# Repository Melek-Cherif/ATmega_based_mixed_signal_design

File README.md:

# ATmega328P Mixed-Signal Design  
*A KiCad PCB project for [Mastering KiCAD: Open source PCB design for beginners] on Coursera.*  

---
## 📷 Preview  
### PCB Layout  

### 3D View  

---

## 📌 Key Features  
- ATmega328P with ADC signal conditioning.  
- Proper decoupling (100nF on ARef, AVCC).  
- Optimized mixed-signal layout.  

---

## 🛠️ Repository Structure  

├── 📂 Mixed_Signal_Design/  
│   ├── 📄 Mixed_Signal_Design.kicad_pro    
│   ├── 📄 Mixed_Signal_Design.kicad_pcb    
│   ├── 📄 Mixed_Signal_Design.kicad_sch    
│   ├── 📂 schematics/
│   │   └── 📄 Mixed_Signal_Design.pdf      
│   └── 📂 fabrication_output/      
│       ├── 📂 BOM/
│       │   └── 📄 Mixed_Signal_Design.csv 
│       └── 📂 gerber/              
│                 
├── 📂 images/                      
│   ├── 📄 3d_view.png              
│   └── 📄 pcb_layout.png       
└── 📄 README.md

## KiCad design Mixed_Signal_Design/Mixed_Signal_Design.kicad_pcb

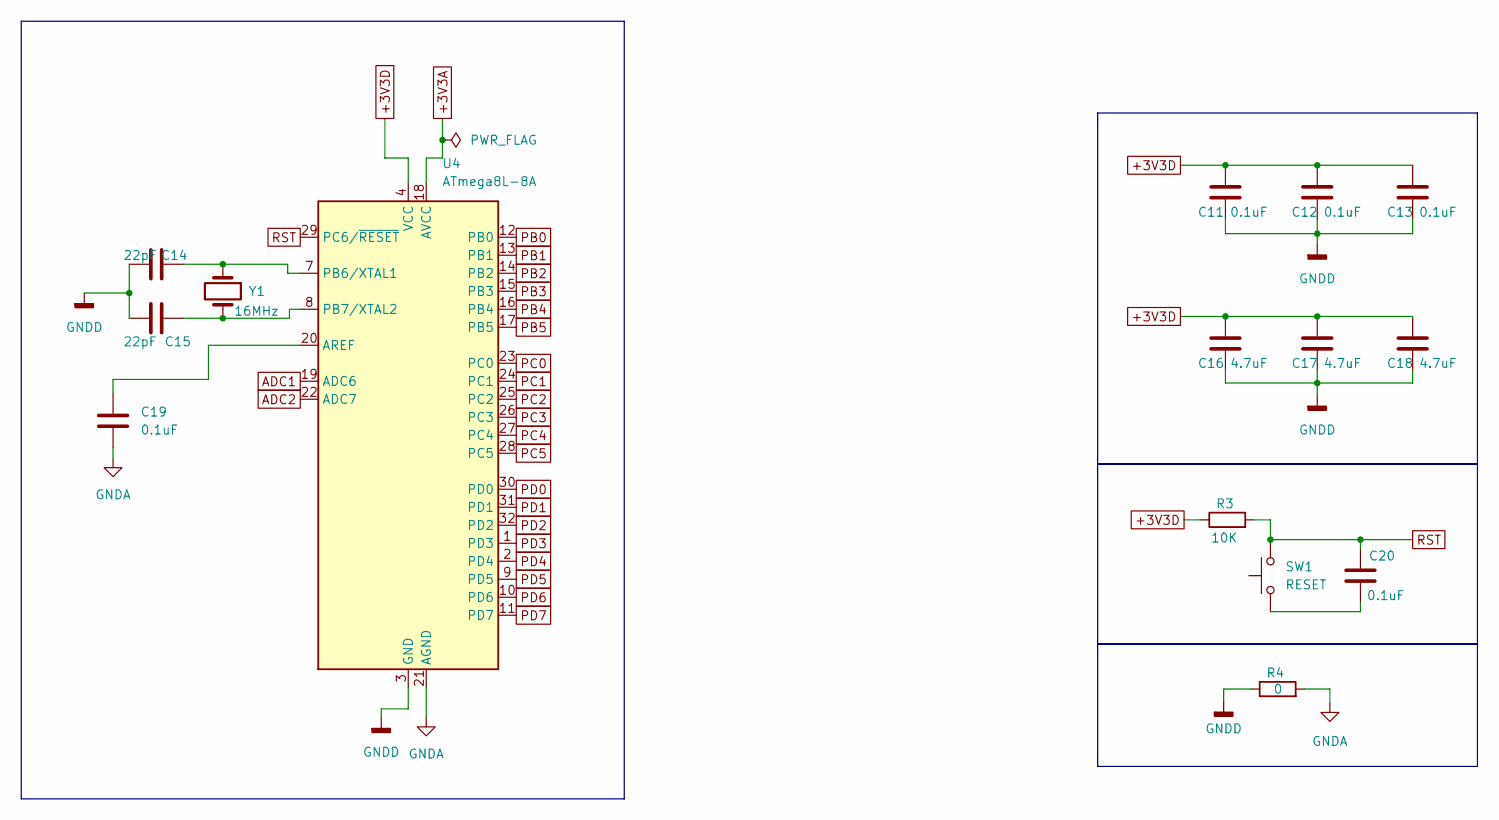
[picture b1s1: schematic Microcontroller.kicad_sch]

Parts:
C11, C12, C13, C19, C20: 0.1uF; C_0603_1608Metric
C14, C15: 22pF; C_0402_1005Metric
C16, C17, C18: 4.7uF; C_0603_1608Metric
R3: 10K; R_0402_1005Metric_Pad0.72x0.64mm_HandSolder
R4: 0; R_0402_1005Metric_Pad0.72x0.64mm_HandSolder
SW1: RESET; SW_SPST_B3U-1000P
U4: ATmega8L-8A; TQFP-32_7x7mm_P0.8mm
Y1: 16MHz; Crystal_SMD_HC49-SD

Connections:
+3V3A: U4.18 (AVCC); also elsewhere on the board
+3V3D: C11.1, C12.1, C13.1, C16.1, C17.1, C18.1, R3.1, U4.4 (VCC), U4.6 (VCC); also elsewhere on the board
ADC1: U4.19 (ADC6); also elsewhere on the board
ADC2: U4.22 (ADC7); also elsewhere on the board
GNDA: C19.1, R4.2, U4.21 (AGND); also elsewhere on the board
GNDD: C11.2, C12.2, C13.2, C14.1, C15.2, C16.2, C17.2, C18.2, R4.1, U4.3 (GND), U4.5 (GND); also elsewhere on the board
unnamed: C20.2, SW1.1 (A), SW1.2 (A)
unnamed: C19.2, U4.20 (AREF)
unnamed: C14.2, U4.7 (PB6/XTAL1), Y1.1
unnamed: C15.1, U4.8 (PB7/XTAL2), Y1.2
PB0: U4.12 (PB0)
PB1: U4.13 (PB1)
PB2: U4.14 (PB2)
PB3: U4.15 (PB3); also elsewhere on the board
PB4: U4.16 (PB4); also elsewhere on the board
PB5: U4.17 (PB5); also elsewhere on the board
PC0: U4.23 (PC0); also elsewhere on the board
PC1: U4.24 (PC1); also elsewhere on the board
PC2: U4.25 (PC2); also elsewhere on the board
PC3: U4.26 (PC3); also elsewhere on the board
PC4: U4.27 (PC4); also elsewhere on the board
PC5: U4.28 (PC5); also elsewhere on the board
PD0: U4.30 (PD0)
PD1: U4.31 (PD1)
PD2: U4.32 (PD2)
PD3: U4.1 (PD3)
PD4: U4.2 (PD4)
PD5: U4.9 (PD5)
PD6: U4.10 (PD6)
PD7: U4.11 (PD7)
RST: C20.1, R3.2, SW1.3 (B), SW1.4 (B), U4.29 (PC6/~RESET); also elsewhere on the board

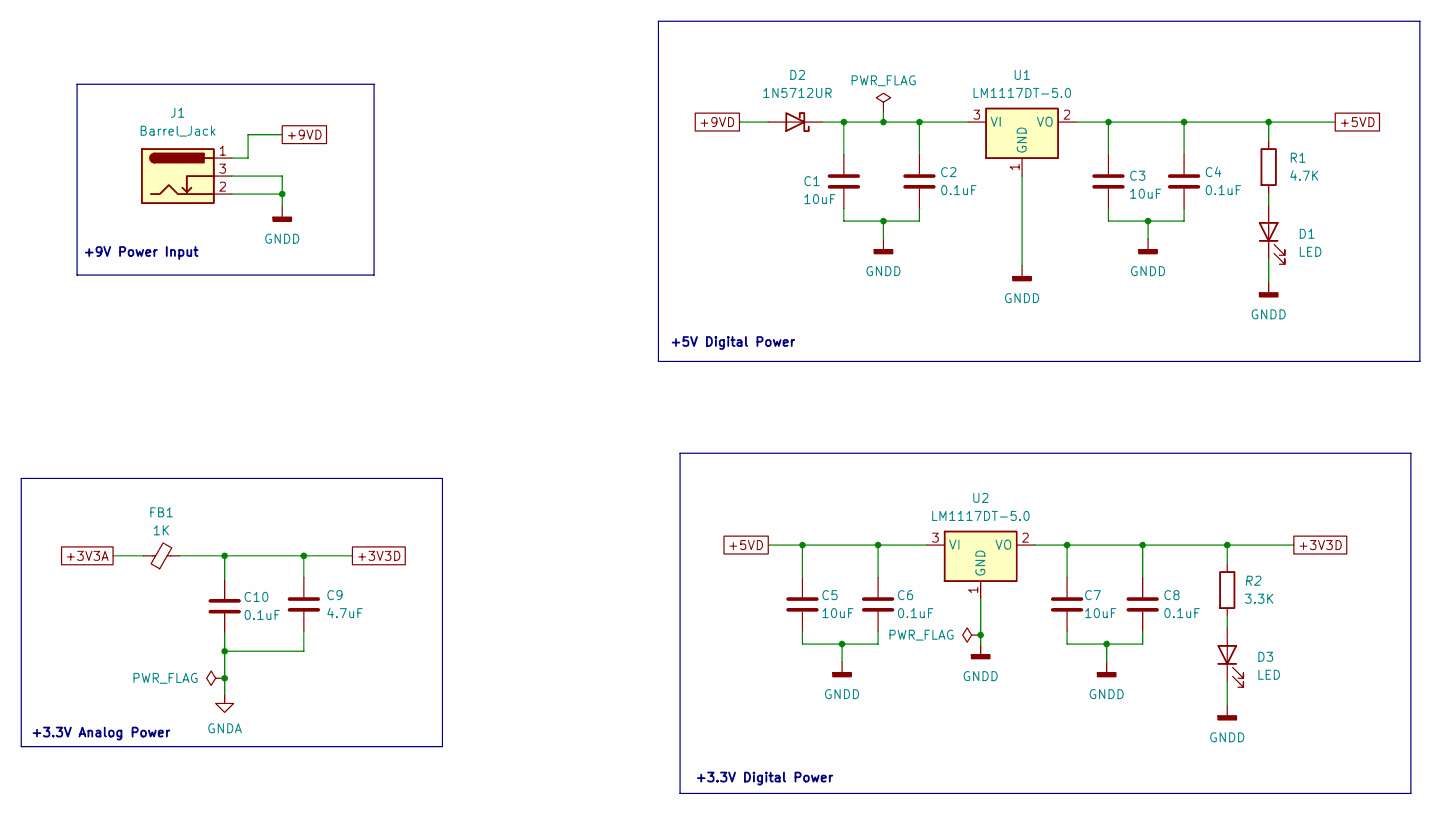
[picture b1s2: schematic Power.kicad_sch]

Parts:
C1, C3, C5, C7: 10uF; C_0603_1608Metric
C2, C4, C6, C8, C10: 0.1uF; C_0603_1608Metric
C9: 4.7uF; C_0603_1608Metric
D1, D3: LED; LED_0603_1608Metric
D2: 1N5712UR; D_MELF
FB1: 1K; FB_MI0805K400R-10
J1: Barrel_Jack; BarrelJack_CUI_PJ-063AH_Horizontal
R1: 4.7K; R_0402_1005Metric_Pad0.72x0.64mm_HandSolder
R2: 3.3K; R_0402_1005Metric_Pad0.72x0.64mm_HandSolder
U1, U2: LM1117DT-5.0; TO-252-3_TabPin2

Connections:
+3V3A: FB1.1; also elsewhere on the board
+3V3D: C7.1, C8.1, C9.1, C10.1, FB1.2, R2.1, U2.2 (VO); also elsewhere on the board
+5VD: C3.1, C4.1, C5.1, C6.1, R1.1, U1.2 (VO), U2.3 (VI)
+9VD: D2.2 (A), J1.1 (PWR)
GNDA: C9.2, C10.2; also elsewhere on the board
GNDD: C1.2, C2.2, C3.2, C4.2, C5.2, C6.2, C7.2, C8.2, D1.1 (K), D3.1 (K), J1.2 (GND), J1.3 (GNDBREAK), U1.1 (GND), U2.1 (GND); also elsewhere on the board
unnamed: D1.2 (A), R1.2
unnamed: C1.1, C2.1, D2.1 (K), U1.3 (VI)
unnamed: D3.2 (A), R2.2

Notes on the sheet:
+3.3V Digital Power
+9V Power Input
+5V Digital Power
+3.3V Analog Power

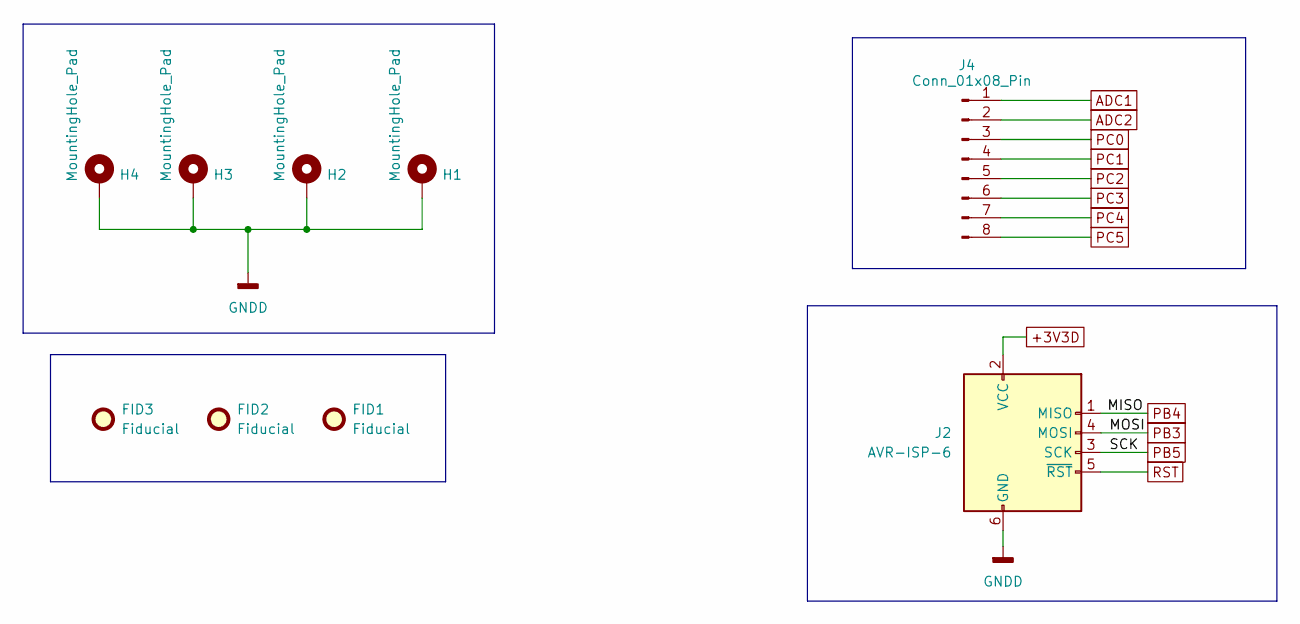
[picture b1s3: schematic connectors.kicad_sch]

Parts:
FID1, FID2, FID3: Fiducial; Fiducial_0.75mm_Mask1.5mm
H1, H2, H3, H4: MountingHole_Pad; MountingHole_2.2mm_M2_ISO7380_Pad
J2: AVR-ISP-6; PinHeader_1x06_P2.54mm_Vertical
J4: Conn_01x08_Pin; PinSocket_1x08_P2.54mm_Vertical

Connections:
+3V3D: J2.2 (VCC); also elsewhere on the board
ADC1: J4.1; also elsewhere on the board
ADC2: J4.2; also elsewhere on the board
GNDD: H1.1, H2.1, H3.1, H4.1, J2.6 (GND); also elsewhere on the board
PB3: J2.4 (MOSI); also elsewhere on the board
PB4: J2.1 (MISO); also elsewhere on the board
PB5: J2.3 (SCK); also elsewhere on the board
PC0: J4.3; also elsewhere on the board
PC1: J4.4; also elsewhere on the board
PC2: J4.5; also elsewhere on the board
PC3: J4.6; also elsewhere on the board
PC4: J4.7; also elsewhere on the board
PC5: J4.8; also elsewhere on the board
RST: J2.5 (~RST); also elsewhere on the board

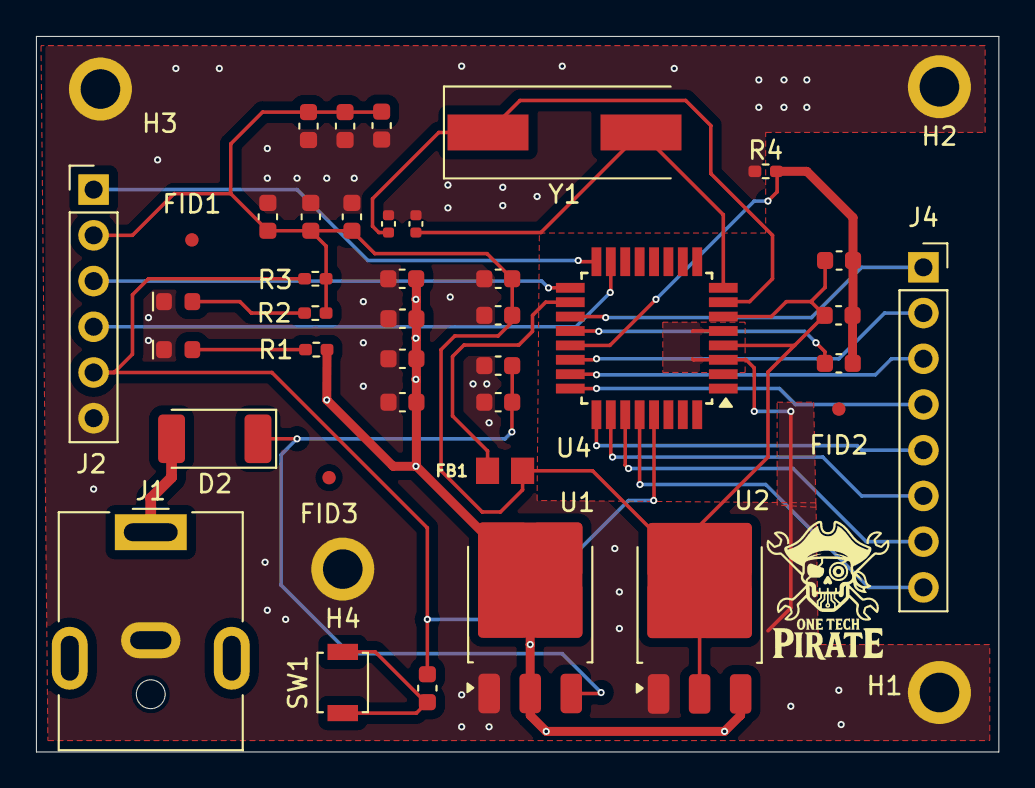
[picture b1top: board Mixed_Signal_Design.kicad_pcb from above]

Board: 4 copper layers, 53.5 x 39.8 mm, 43 parts (0 on the bottom side), 25 nets.

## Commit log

2025-04-15 init commit
2025-04-17 commit
    adding power and microcontroller schematics
